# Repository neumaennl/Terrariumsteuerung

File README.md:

# Steuerungsskript für mein Terrarium

Die Steuerung läuft hauptsächlich auf einem [ESP32-C3 SuperMini mit Display](https://de.aliexpress.com/item/1005007929382296.html).

Daran angeschlossen sind:

- [SHT40](https://sensirion.com/de/produkte/katalog/SHT40) (vorher [GYBMEP BME280](https://42project.net/shop/sensoren/temperatursensoren/temperatur-feuchtigkeits-luftdruck-i2c-sensor/)) Sensor für Luftfeuchtigkeit und Temperatur (kommuniziert über [I²C](https://de.wikipedia.org/wiki/I%C2%B2C))
- 2 [KY-019](https://www.elektronik-kompendium.de/sites/praxis/bauteil_relaisboard.htm) Relais Module, um die Stromversorgung für Lüfter und Beregnungsanlage zu steuern
- 2 4-Pin CPU Lüfter

Auf einem Raspberry Pi 2 läuft eine Web GUI, über die historische Daten angezeigt werden und Einstellungen verändert werden können. Dazu kommuniziert der Raspberry Pi mit dem ESP32 via REST Schnittstelle. Dieser Teil ist allerdings vollkommen optional und für die eigentliche Steuerung absolut nicht notwendig.

## Autostart

Damit das Skript garantier immer läuft, wurde ein systemd Service erstellt.  
Dazu `terrarium.service` nach `/etc/systemd/system/` kopieren.  
Dann über `sudo systemctl daemon-reload` systemd neu laden.  
Mit `sudo systemctl enable terrarium.service` den Dienst aktivieren (damit er beim hochfahren startet) und wenn gewünscht per `sudo systemctl start terrarium.service` sofort starten.

Optional können für die Historie Umgebungsvariablen im Service gesetzt werden:

- `TERRARIUM_RETENTION_DAYS` (Standard: `31`) löscht nur Daten, die älter als X Tage sind.
- `TERRARIUM_RECENT_WINDOW_DAYS` (Standard: `3`) definiert, wie lange Daten in hoher Auflösung gespeichert werden.
- `TERRARIUM_RECENT_RESOLUTION_SECONDS` (Standard: `30`) Auflösung innerhalb des Recent-Fensters.
- `TERRARIUM_ARCHIVE_RESOLUTION_SECONDS` (Standard: `900`) Auflösung fuer ältere Daten.
- `TERRARIUM_MAX_DB_ROWS` begrenzt die Gesamtzahl Datensaetze (Standard wird aus obigen Werten berechnet).

Beispiel in `terrarium.service` unter `[Service]`:

```ini
Environment=TERRARIUM_RETENTION_DAYS=31
Environment=TERRARIUM_RECENT_WINDOW_DAYS=3
Environment=TERRARIUM_RECENT_RESOLUTION_SECONDS=30
Environment=TERRARIUM_ARCHIVE_RESOLUTION_SECONDS=900
Environment=TERRARIUM_MAX_DB_ROWS=12000
```

## Abhängigkeiten

- [offizieller SSD1306 Display Treiber](https://www.google.com/search?q=https://github.com/micropython/micropython/blob/master/drivers/display/ssd1306.py)
- [BME280 Treiber](https://github.com/robert-hh/BME280/blob/master/bme280_float.py)
- [SHT40 Treiber](https://github.com/jposada202020/MicroPython_SHT4X/blob/master/micropython_sht4x/sht4x.py)

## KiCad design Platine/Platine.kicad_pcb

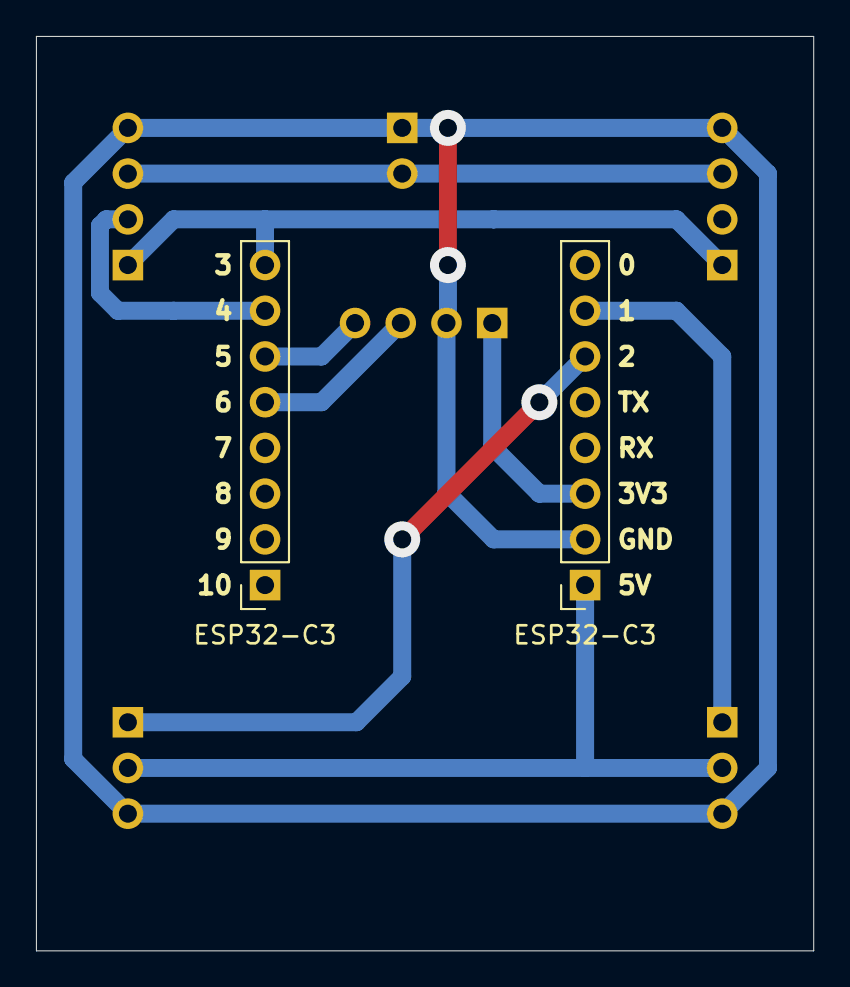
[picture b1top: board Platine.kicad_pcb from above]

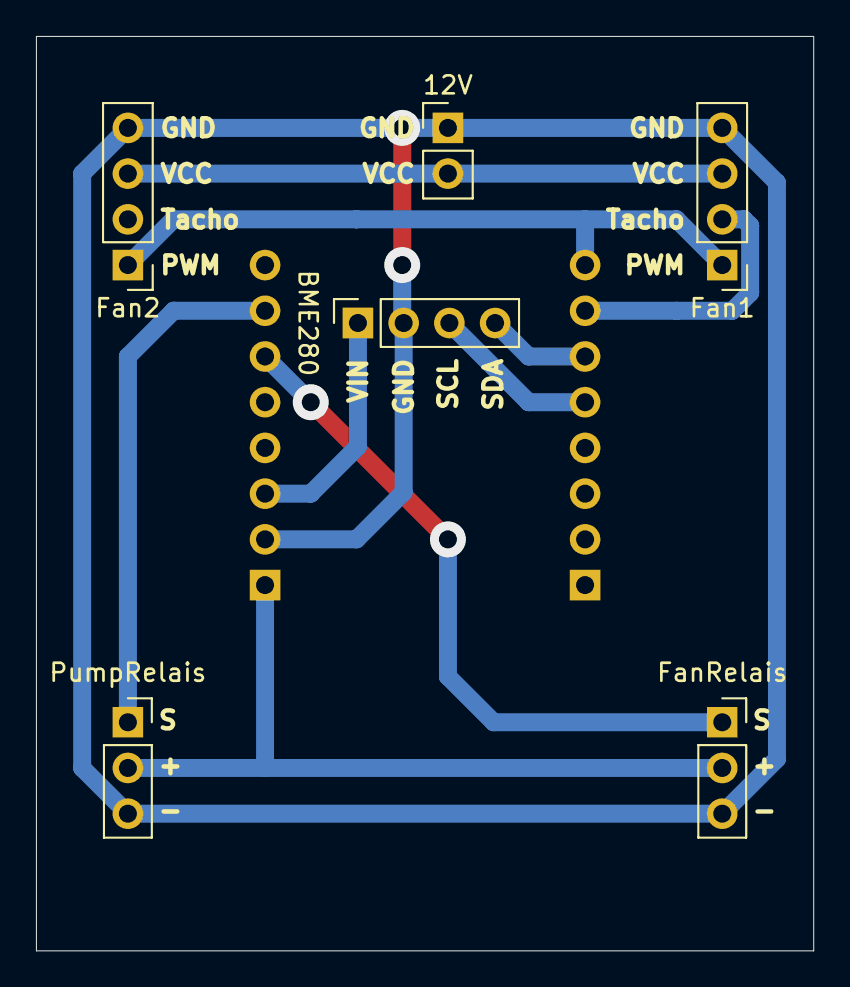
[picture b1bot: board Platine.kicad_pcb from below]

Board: 2 copper layers, 43.2 x 50.8 mm, 8 parts (6 on the bottom side), 10 nets.

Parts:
12V: 12V; PinHeader_1x02_P2.54mm_Vertical
BME280: BME280; PinSocket_1x04_P2.54mm_Vertical
ESP32-C3: ESP32-C3 left; PinSocket_1x08_P2.54mm_Vertical
ESP32-C3#2: ESP32-C3 right; PinSocket_1x08_P2.54mm_Vertical
Fan1: Fan 1; PinHeader_1x04_P2.54mm_Vertical
Fan2: Fan 2; PinHeader_1x04_P2.54mm_Vertical
FanRelais: Fan Relais; PinSocket_1x03_P2.54mm_Vertical
PumpRelais: Pump Relais; PinSocket_1x03_P2.54mm_Vertical

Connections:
3V3: BME280.1, ESP32-C3#2.3
5V: ESP32-C3#2.1, FanRelais.2, PumpRelais.2
12V: 12V.2, Fan1.3, Fan2.3
Fan_PWM: ESP32-C3.8, Fan1.1, Fan2.1
Fan_Relais: ESP32-C3#2.6, FanRelais.1
Fan_Tacho: ESP32-C3.7, Fan1.2
GND: 12V.1, BME280.2, ESP32-C3#2.2, Fan1.4, Fan2.4, FanRelais.3, PumpRelais.3
Pump_Relais: ESP32-C3#2.7, PumpRelais.1
SCL: BME280.3, ESP32-C3.5
SDA: BME280.4, ESP32-C3.6

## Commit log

2026-01-28 Fritzing Dateien hinzugefügt
2026-02-02 Web GUI hinzugefügt
2026-02-04 Pfad korrigiert
2026-02-04 Intervalle für Datenspeicherung angepasst und Diagramm in der GUI zoombar gemacht.
2026-02-11 Schaltplan auf ESP32-C3 SuperMini mit Display umgestellt
2026-02-11 Readme für ESP32-C3 umgeschrieben
2026-02-15 Code nach MicroPython portiert
2026-02-15 CHunking für History
2026-02-15 RPM Berechnung gefixed
2026-02-15 responsive Anpassungen
2026-02-15 Platine Start
2026-02-15 Platine hat alle Netze
2026-02-18 Anpassungen für geringeren Arbeitsspeicher Verbrauch
2026-02-20 Behandlung für Zeitzonen und Sommerzeit hinzugefügt
2026-02-20 Platine finalisiert
2026-02-22 vertauschte PWM und Tacho Pins korrigiert
2026-02-26 beide Varianten in einem Branch als Basis für Refactoring zu getrennten Verantwortlichkeiten
2026-02-26 getrennte Verantwortlichkeiten für Raspberry Pi und ESP32-C3 implementiert
2026-02-28 kleine Fixes
2026-03-05 Steuerung der Beregnungsanlage per Button hinzugefügt.
2026-03-05 removed obsolete code
2026-03-05 Schreiben von Datenbankeinträgen gefixed
2026-03-05 Diagramm holt nun dynamisch Daten, Werte von Lüfter und Pumpe werden im Diagramm angezeigt und Speicherstatus vom ESP wird bei den Werten angezeigt.
2026-03-07 Hysterese für Lüfter
2026-03-08 Lüfter läuft in der Nacht nicht
2026-03-11 separate Nachtzeiten für Lüfter und Pumpe
2026-03-15 Unterstützung für den SHT40 Temperatur- und Luftfeuchtigkeitssensor hinzugefügt
2026-03-16 Aufräumarbeiten
2026-03-20 Doku aktualisiert
